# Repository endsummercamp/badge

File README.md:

# Badge

Per l'anno 2024 anche l'End Summer Camp si vuole dotare di un badge interattivo e programmabile, in linea con gli eventi simili internazionali.

## Attuale livello di completamento

- [x] Definizione dei requisiti: 70%
- [ ] Progettazione hardware: 16%
- [ ] Design grafico / artistico: 0%
- [ ] Firmware: 0%

## Obiettivi ad alto livello

- [ ] Il badge non sarà annuale, ma riutilizzabile per tutti gli eventi futuri
- [ ] Il badge dovrà (tentare di) avere un utilità anche al di fuori dell'evento
- [ ] Evitare costi e impatti ambientali inutili, preferire batterie 18650 o stilo per facile riutilizzo, dimensioni ridotte

## Come contribuire

1. Presentarsi nel gruppo telegram https://t.me/endsummercamp
1. L'EDA di riferimento KiCad 8, scaricabile da https://www.kicad.org/
1. Il firmware sarà basato sul linguaggio Rust

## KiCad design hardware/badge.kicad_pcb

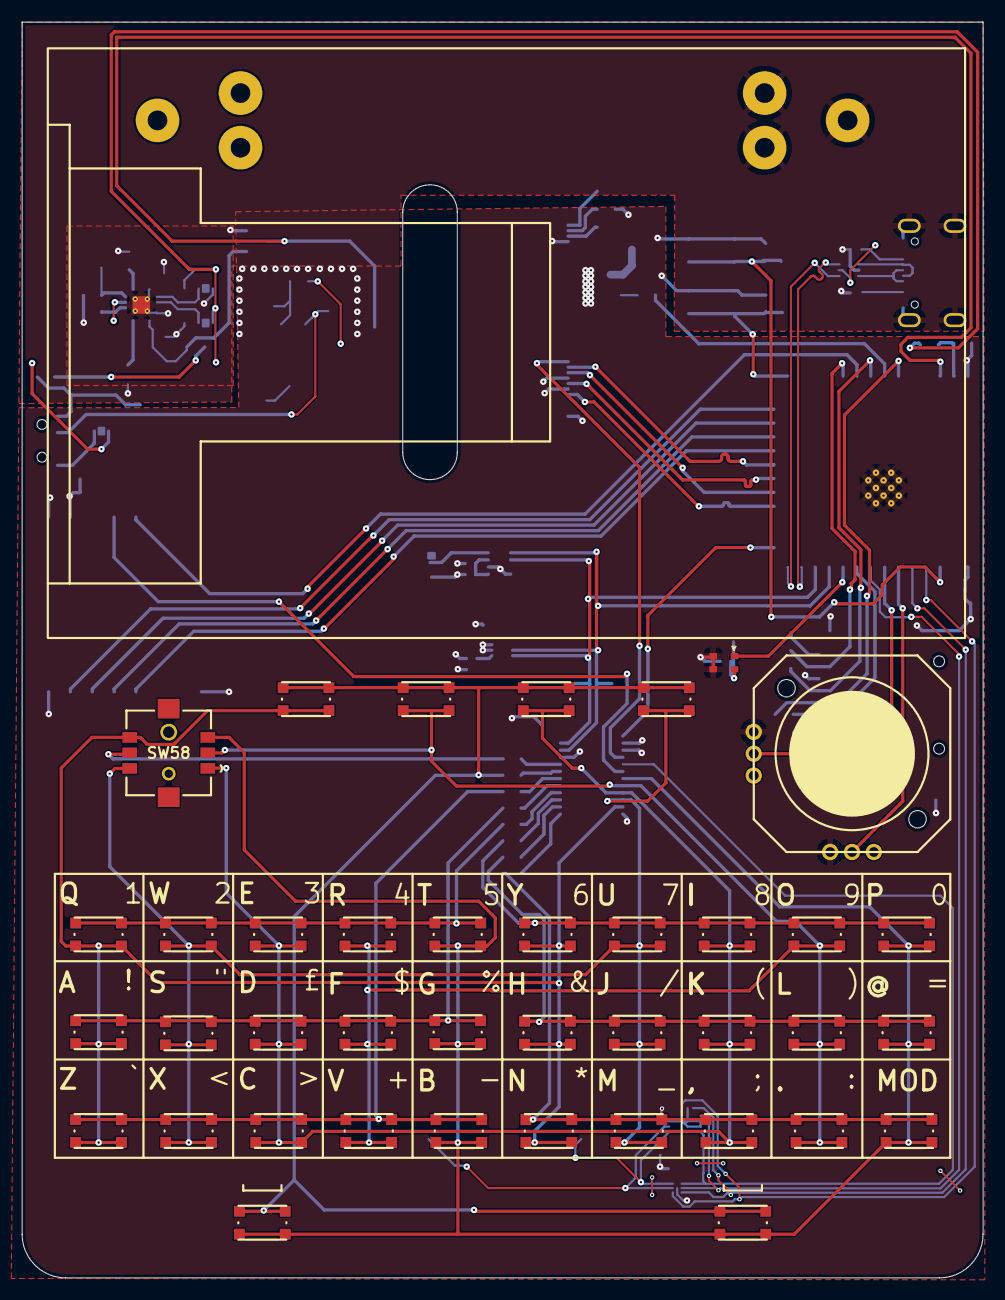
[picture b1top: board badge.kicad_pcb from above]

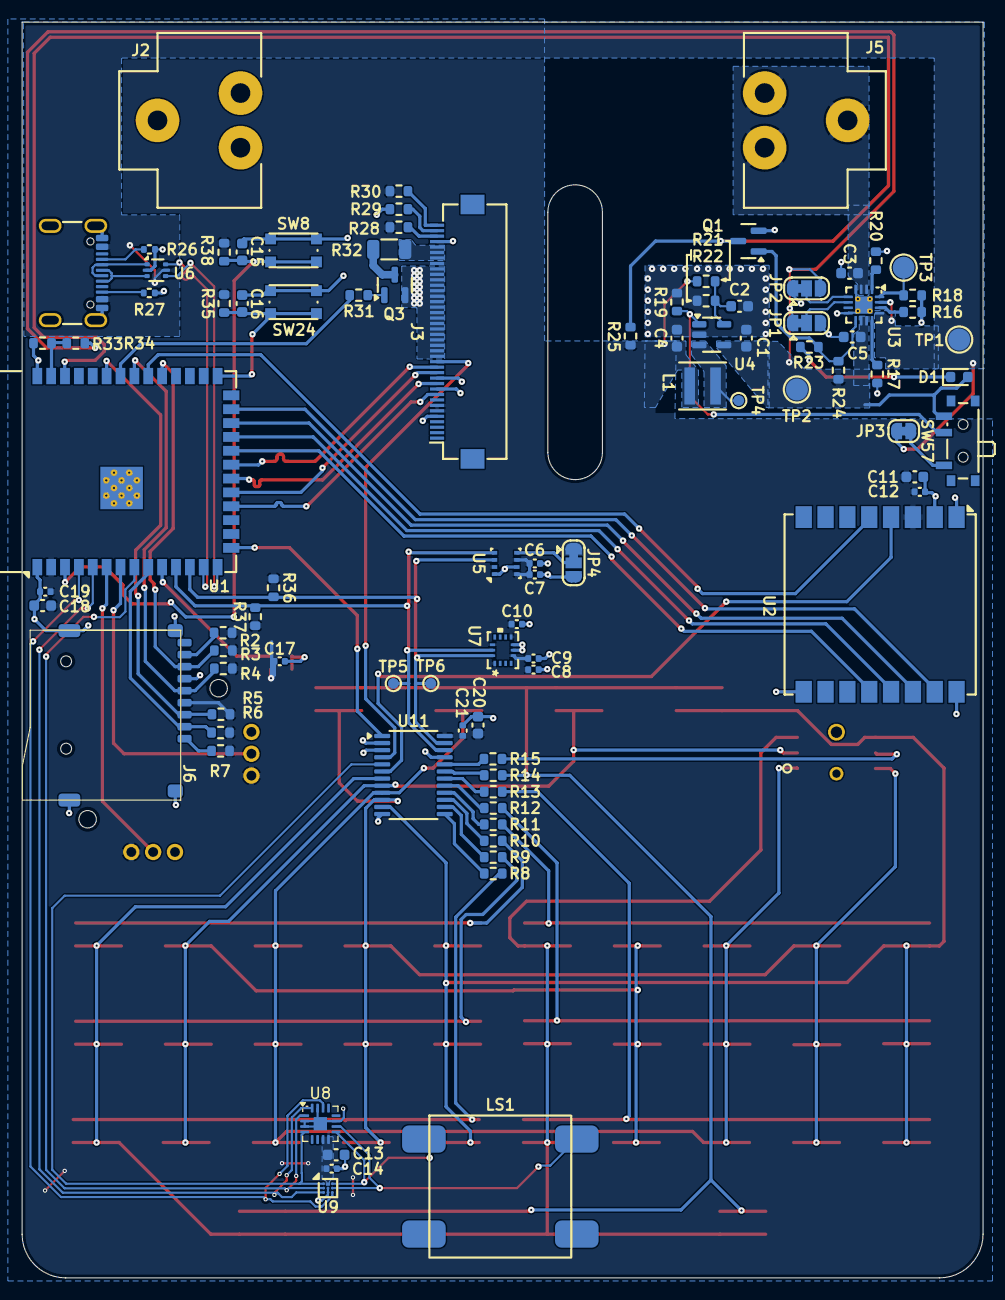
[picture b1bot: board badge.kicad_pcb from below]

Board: 2 copper layers, 88.0 x 115.0 mm, 131 parts (91 on the bottom side), 85 nets.

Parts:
C1, C3, C5: 4.7uF; C_0603_1608Metric
C2: TBD; C_0603_1608Metric
C4, C11, C13, C15, C16, C18, C20: 10uF; C_0603_1608Metric
C6, C7, C9, C10, C12, C17, C19, C21: 100nF 6.3V; C_0402_1005Metric
C8: 1uF 25V; C_0402_1005Metric
C14: 100nF; C_0402_1005Metric
D1: LED; LED_0603_1608Metric
FID1: DISPLAY; display
J2, J5: MY-18650-01
J3: Conn_01x40; Hirose_FH12-40S-0.5SH_1x40-1MP_P0.50mm_Horizontal
J4: USB_C_Receptacle_USB2.0_14P; USB_C_Receptacle_GCT_USB4105-xx-A_16P_TopMnt_Horizontal
J6: Micro_SD_Card_Det1; TF-01A
JP1: EN1; SolderJumper-3_P1.3mm_Bridged12_RoundedPad1.0x1.5mm
JP2: EN2; SolderJumper-3_P1.3mm_Bridged12_RoundedPad1.0x1.5mm
JP3: Grumpy wifasoi jumper; SolderJumper-2_P1.3mm_Bridged_RoundedPad1.0x1.5mm
JP4: SolderJumper_3_Bridged12; SolderJumper-3_P1.3mm_Bridged12_RoundedPad1.0x1.5mm
L1: 2.2uH; L_Coilcraft_XxL4040
LS1: 8Ω@1W; KLJ-01304T-08R07W
MK1: Microphone_Crystal; microfono
Q1, Q3: AO3400A; SOT-23
R2, R3, R4, R5, R6, R7, R19, R20, R24, R25, R35, R38: 47K; R_0603_1608Metric
R8, R9, R10, R11, R12, R13, R14, R15: 22; R_0603_1608Metric
R16, R28, R29, R30: 0R; R_0603_1608Metric
R17, R36, R37: 1.2K; R_0603_1608Metric
R18: 1.78K; R_0603_1608Metric
R21: 680K; R_0603_1608Metric
R22, R33, R34: 150K; R_0603_1608Metric
R23: 330R; R_0603_1608Metric
R26, R27: 5.1K; R_0402_1005Metric
R31: 100R; R_0603_1608Metric
R32: 12R; R_1206_3216Metric
RV1: R_Potentiometer_Dual_Separate; JOYSTICK_ANALOG_MINITHM
SW1, SW2, SW3, SW4, SW5, SW6, SW7, SW9, SW10, SW11, SW12, SW13, SW14, SW15, SW16, SW17, SW18, SW19, SW20, SW21, SW22, SW23, SW25, SW26, SW27, SW28, SW29, SW30, SW31, SW33, SW34, SW35, SW36, SW37, SW38, SW39: SW_Push; bottonepiccolo_C2888430
SW8: RST; bottonepiccolo_C2888430
SW24: BOOT; bottonepiccolo_C2888430
SW57: MK-12C02-G020; SW_SPDT_PCM12
SW58: SKRHABE010; SKRHABE010_ALPS
TP1, TP2, TP3: TestPoint; TestPoint_Pad_D2.0mm
TP4: TestPoint; TestPoint_Pad_D1.0mm
TP5: SCL; TestPoint_Pad_D1.0mm
TP6: SDA; TestPoint_Pad_D1.0mm
U1: ESP32-S3-WROOM-1
U2: Ai-Thinker-Ra-02; Ai-Thinker-Ra-01-LoRa
U3: BQ24075RGT; VQFN-16-1EP_3x3mm_P0.5mm_EP1.6x1.6mm_ThermalVias
U4: TLV62569DBV; SOT-23-5
U5: BME280; Bosch_LGA-8_2.5x2.5mm_P0.65mm_ClockwisePinNumbering
U6: USBLC6-2P6; SOT-666
U7: BMI270; BMI270_BOS
U8: MAX98357A; TQFN-16-1EP_3x3mm_P0.5mm_EP1.23x1.23mm
U9: MAX98357A; WLP-9_1.448x1.468mm_Layout3x3_P0.4mm_Ball0.27mm_Pad0.25mm
U11: PCA9555PW; TSSOP-24_4.4x7.8mm_P0.65mm

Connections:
+3.3V: C4.1, C6.1, C7.1, C8.1, C9.1, C10.1, C11.1, C12.1, C13.1, C14.1, C17.1, C18.1, C19.1, C20.1, C21.1, J3.6, J3.7, J3.33, J6.4 (VDD), JP4.1 (A), L1.2, MK1.4 (-), R2.1, R3.1, R4.1, R5.1, R6.1, R7.1, R21.1, R25.2, R28.2, R30.1, R35.1, R36.1, R37.1, R38.1, RV1.1, RV1.4, U1.2 (3V3), U2.3 (VDD), U5.2 (CSB), U5.6 (VDDIO), U5.8 (VDD), U7.1 (SDO), U7.5 (VDDIO), U7.8 (VDD), U7.12 (CSB), U8.7 (VDD), U8.8 (VDD), U9.A2 (VDD), U11.24 (VDD)
/AUDIO.BCLK: U1.5 (IO5), U8.16 (BCLK), U9.C1 (BCLK)
/AUDIO.LRCLK: U1.4 (IO4), U8.14 (LRCLK), U9.C3 (LRCLK)
/AUDIO.SD: U1.8 (IO15), U8.1 (DIN), U9.B1 (DIN)
/LCD.CLK: J3.11, U1.20 (IO12)
/LCD.CS: J3.9, U1.18 (IO10)
/LCD.MISO: J3.14, U1.21 (IO13)
/LCD.MOSI: J3.13, U1.19 (IO11)
/LORA.CLK: U1.22 (IO14), U2.12 (SCK)
/LORA.CS: U1.25 (IO48), U2.15 (~NSS)
/LORA.MISO: U1.23 (IO21), U2.13 (MISO)
/LORA.MOSI: U1.24 (IO47), U2.14 (MOSI)
/audio/MUTE: U8.4 (~SD_MODE), U9.A1 (~SD_MODE), U11.5 (IO0_1)
/imu/SCL: R37.2, TP5.1, U1.11 (IO18), U5.4 (SCK), U7.13 (SCX), U11.22 (SCL)
/imu/SDA: R36.2, TP6.1, U1.12 (IO8), U5.3 (SDI), U7.14 (SDX), U11.23 (SDA)
/keyboard/IO_IRQ: U1.15 (IO3), U11.1 (~INT)
/keyboard/LCD_RESET: J3.15, U11.4 (IO0_0)
/keyboard/LORA_CE: U2.4 (~RESET), U11.6 (IO0_2)
/lcd/BACKLIGHT: R31.1, U1.34 (IO41)
/lcd/IM0: J3.38, R28.1
/lcd/IM1: J3.39, R29.2
/lcd/IM2: J3.40, R30.2
/lcd/LEDK: J3.34, J3.35, J3.36, R32.2
/mcu/BOOT: C16.1, R35.2, SW24.2, U1.27 (IO0)
/mcu/CHG: Q1.3 (D), R25.1, U1.38 (IO2)
/mcu/LORA_IRQ: U1.32 (IO39), U2.5 (DIO0)
/mcu/MIC: MK1.1 (+), U1.10 (IO17)
/mcu/RST: C15.1, R38.2, SW8.2, U1.3 (EN)
/mcu/SD_CLK: J6.5 (CLK), R4.2, U1.33 (IO40)
/mcu/SD_CMD: J6.3 (CMD), R5.2, U1.35 (IO42)
/mcu/SD_CS: J6.2 (DAT3/CD), R6.2, U1.9 (IO16)
/mcu/SD_D0: J6.7 (DAT0), R3.2, U1.31 (IO38)
/mcu/USB_D+: U1.14 (IO20), U6.4 (I/O2)
/mcu/USB_D-: U1.13 (IO19), U6.6 (I/O1)
/mcu/VBAT_DIV2: R33.1, R34.2, U1.39 (IO1)
/mcu/XOUT: RV1.5, U1.7 (IO7)
/mcu/YOUT: RV1.2, U1.6 (IO6)
/power/EN1: JP1.2 (C), U3.6 (EN1)
/power/EN2: JP2.2 (C), U3.5 (EN2)
/power/ISET: R18.1, TP3.1, U3.16 (ISET)
/power/~CHG: Q1.1 (G), R23.1, R24.1, U3.9 (~CHG)
GND: C1.2, C2.2, C3.2, C4.2, C5.2, C6.2, C7.2, C8.2, C9.2, C10.2, C11.2, C12.2, C13.2, C14.2, C15.2, C16.2, C17.2, C18.2, C19.2, C20.2, C21.2, J2.1, J3.5, J3.10, J3.12, J3.16, J3.17, J3.18, J3.19, J3.20, J3.21, J3.22, J3.23, J3.24, J3.25, J3.26, J3.27, J3.28, J3.29, J3.30, J3.31, J3.32, J3.37, J4.A1 (GND), J4.A12 (GND), J4.B1 (GND), J4.B12 (GND), J4.S1 (SHIELD), J6.6 (VSS), J6.10 (SHIELD), JP1.3 (B), JP2.1 (A), JP4.3 (B), MK1.2 (-), MK1.3 (-), Q1.2 (S), Q3.2 (S), R16.2, R17.2, R18.2, R19.1, R20.2, R22.2, R26.2, R27.2, R29.1, R33.2, RV1.3, RV1.6, SW8.1, SW24.1, U1.1 (GND), U1.40 (GND), U1.41 (GND), U2.1 (GND), U2.2 (GND), U2.9 (GND), U2.16 (GND), U3.4 (~CE), U3.8 (VSS), U3.17 (VSS), U4.2 (GND), U5.1 (GND), U5.7 (GND), U6.2 (GND), U7.6 (GNDIO), U7.7 (GND), U8.2 (GAIN_SLOT), U8.3 (GND), U8.11 (GND), U8.15 (GND), U8.17 (PAD), U9.B2 (GAIN_SLOT), U9.C2 (GND), U11.2 (A1), U11.3 (A2), U11.12 (VSS), U11.21 (A0)
unnamed: D1.1 (K), R23.2
unnamed: J4.A5 (CC1), R26.1
unnamed: J4.B5 (CC2), R27.1
unnamed: J4.A6 (D+), J4.B6 (D+), U6.3 (I/O2)
unnamed: J4.A7 (D-), J4.B7 (D-), U6.1 (I/O1)
unnamed: C3.1, J5.1, U3.2 (BAT), U3.3 (BAT)
unnamed: J6.8 (DAT1), R2.2
unnamed: J6.1 (DAT2), R7.2
unnamed: JP3.2 (B), SW57.1 (A)
unnamed: JP4.2 (C), U5.5 (SDO)
unnamed: Q3.3 (D), R32.1
unnamed: Q3.1 (G), R31.2
unnamed: R8.2, SW1.1, SW9.1, SW17.1, SW25.1, SW33.1
unnamed: R9.2, SW2.1, SW10.1, SW18.1, SW26.1, SW34.1
unnamed: R10.2, SW3.1, SW11.1, SW19.1, SW27.1, SW35.1
unnamed: R11.2, SW4.1, SW12.1, SW20.1, SW28.1, SW36.1
unnamed: R12.2, SW5.1, SW13.1, SW21.1, SW29.1, SW37.1
unnamed: R13.2, SW6.1, SW14.1, SW22.1, SW30.1, SW38.1
unnamed: R14.2, SW7.1, SW15.1, SW16.1, SW23.1, SW31.1, SW39.1
unnamed: R15.2, SW58.5
unnamed: R19.2, SW57.2 (B), U4.1 (EN)
unnamed: R17.1, U3.12 (ILIM)
unnamed: R16.1, U3.14 (TMR)
unnamed: R20.1, U3.1 (TS)
unnamed: C2.1, R21.2, R22.1, U4.5 (FB)
unnamed: L1.1, TP4.1, U4.3 (SW)
unnamed: LS1.1, U8.10 (OUTN), U9.B3 (OUTN)
unnamed: LS1.2, U8.9 (OUTP), U9.A3 (OUTP)
unnamed: SW16.2, SW33.2, SW34.2, SW35.2, SW36.2, SW37.2, SW38.2, SW39.2, SW58.3, U11.7 (IO0_3)
unnamed: SW25.2, SW26.2, SW27.2, SW28.2, SW29.2, SW30.2, SW31.2, SW58.2, U11.8 (IO0_4)
unnamed: SW17.2, SW18.2, SW19.2, SW20.2, SW21.2, SW22.2, SW23.2, SW58.1, U11.9 (IO0_5)
unnamed: SW9.2, SW10.2, SW11.2, SW12.2, SW13.2, SW14.2, SW15.2, SW58.4, U11.10 (IO0_6)
unnamed: SW1.2, SW2.2, SW3.2, SW4.2, SW5.2, SW6.2, SW7.2, SW58.6, U11.11 (IO0_7)
unnamed: R8.1, U11.13 (IO1_0)
unnamed: R9.1, U11.14 (IO1_1)
unnamed: R10.1, U11.15 (IO1_2)
unnamed: R11.1, U11.16 (IO1_3)
unnamed: R12.1, U11.17 (IO1_4)
unnamed: R13.1, U11.18 (IO1_5)
unnamed: R14.1, U11.19 (IO1_6)
unnamed: R15.1, U11.20 (IO1_7)
VSYS: C1.1, C5.1, D1.2 (A), JP1.1 (A), JP2.3 (B), R24.2, R34.1, SW57.3 (C), TP2.1, U3.10 (OUT), U3.11 (OUT), U4.4 (VIN)
VUSB: J4.A4 (VBUS), J4.A9 (VBUS), J4.B4 (VBUS), J4.B9 (VBUS), JP3.1 (A), TP1.1, U3.13 (IN), U3.15 (SYSOFF), U6.5 (VBUS)

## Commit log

2024-04-10 move hw in subdirectory
2024-04-10 add readme
2024-04-10 add lcd sch
2024-04-11 Add the battery charger
    This commit will remove the old battery switching logic, and replace it
    with a BQ24075.
    Some more info are required, so the component that need a value are marked as TBD
2024-04-11 Create LICENSE
2024-04-11 kiri ci
2024-04-11 sposta mcu a destra
2024-04-11 fork kiri action
2024-04-11 ditch ci
2024-04-16 add ch340g
2024-04-16 chg pin
2024-04-16 fix ch340
2024-04-16 keyboard schematic
2024-04-17 Make the badge power on on usb connected
    Fix charge led polarity :D
    Isolate more the CHG signal from the BQ24075
2024-04-17 rename power symbols, power switch on EN pin instead of VIN
2024-05-01 remove ch340
2024-05-05 update usb port, esd, lcsc
2024-05-05 remove global labels
2024-05-05 en pullup
2024-05-05 add imu BMI270
2024-05-07 add bme280
2024-05-07 set footprints, some lcsc codes
2024-05-14 Initial schema of LCD interface
2024-05-16 lcd wires, wire direction
2024-05-16 battery voltage divider
2024-05-16 Calculate approximate value of LED resistor
2024-05-17 Fix resistor value, fix error in schematic
    Pin 37 was incorrectly bunched with the backlight LED cathodes, but is
    actually a GND pin.
2024-05-18 display, switches, (switch)joystick footprint
2024-05-18 joystick collegato, tastiera aggiornata, modulo lora, layout preliminare
2024-05-18 move voltage divider from bat to vsys
2024-05-18 Calculate the resistor values for the BMS
2024-05-18 use AO3400A in place of the npn
2024-05-18 do not use gpio 45 and 46
2024-05-18 add boot button
2024-05-18 Add audio subsystem
    This adds a speaker and an I2s DAC+amplifier based on MAX98357A
2024-05-18 Add footprint for the speaker
    As the datashet is a bit shite, we need to check the footprint
    if we stai with the speaker i selected.
2024-05-19 Fix pin mapping, pin 3/4 are now named "NC"
2024-05-19 Fix gain selector resistor footprint
2024-05-19 keyboard demo
2024-05-19 add PCA9555PW io expander
2024-05-19 group things in layout
2024-05-20 fix sda scl
2024-05-20 remove lcd reset short circuit to gnd
2024-05-21 First draft of the BMS routing
    TODO: check VDD pèoer flag in schematic
2024-05-21 Routhe BMS subsystem
    Fix the JP1 and JP2 power net
2024-05-21 Add CHG led
2024-05-21 Bms routing (#16)
    Routhe BMS subsystem
    Fix the JP1 and JP2 power net
2024-05-22 Route the audio subsystem
    Fix BMS routing
    Remove audio gain selection, to relax routing
    Add DRC rule for JLC
    Add custom rule for Audio BGA routing
2024-05-23 Start Routing of power subsystem
    Start routing of lcd and sd card, only for checking if pin swaps are
    needed
2024-05-26 add adafruit joystick
2024-05-26 remove mux, use i2c expander for keyboard
2024-05-26 reorganize keyboard buttons for layout
2024-05-26 add (analog) mems microphone
2024-05-27 Add MY-18650-01 footprint and 3d model
2024-05-27 Move battery on top
2024-05-27 add firmware directory
2024-05-28 Create a preliminary routing
    Disconnect the LORA module from the lcd bus
    Add netclass and lenght matching rule for the LCD signals
    Use Bus for spi syglas for easy netclass association
    Remove cutaway jumper for the io expansions, and hardcode the address
    Routed the keyboard matrix
    Change the LCD resistor to 1202
2024-05-28 draw the italian flag on lcd rgb888 🫡
2024-05-29 Move usb to the opposite side of the PCB
    Change the lcd SPI pins and use ones dirrectly atatched to SPI2
    Lengh tune the LCD spi line and USB
2024-05-29 Route I2C bus
    Add decoupling capacitors to esp32 and io expandes
2024-05-29 Add lora module 3d model
2024-05-30 Cleanup project library
    Add hexpansion connector symbol, footprint and 3d
2024-05-30 Remove tildadragon lib
    commited as my mistake
2024-05-31 [firmware] change from esp32-c3 to esp32-s3
2024-05-31 Add button 3D models
2024-05-31 Add alps joystic 3d model
2024-05-31 Add analog joystick 3D model
2024-06-04 Add sdcard fooprint
    Remove io expander
    Reorganize a bit the mcu schematic
    Routed audio
    Routed lora
    Partial pin swapping of esp32 for facilitating routing
2024-06-05 Route all board
    Fix CS missing for SD card
    Add IMU symbol and footprint to the project lib
    Finish esp32 pinswaps
    Move non critical signals to the keyboard IO expander
    Add power flag symbols
    Fix Dpad pin type
2024-06-06 Associate all LCSC component
    Change sdcard pullup resistor to 47K
    Center main schematic
2024-06-06 Fix via anular ring
    Fix position of colliding components
    Add mic pin 1 marker manually
2024-06-11 Fix sd card footprint
2024-06-13 Fix mic footprint
2024-06-25 Beautified schematic, added I2C addresses
2024-07-01 update bom, correct jlcpcb rotation
2024-07-02 Fix rotation and position offset of components
    Fix lora module rotation
    Fix esp32 module position offset
    Fix sd card position offset
2024-07-05 Fix audio chip power pin in schematic
    Add the motherfucker in project library
2024-07-22 add joystick lcsc code
2024-07-22 add joystick lcsc code, for real
2024-07-25 fix lcsc code for fpc (wrong but somewhat compatible footprint)
2024-07-25 remove references from front silkscreen
2024-07-25 dual footprint for audio amp
2024-07-29 update lcsc codes to use (new?) basic components
